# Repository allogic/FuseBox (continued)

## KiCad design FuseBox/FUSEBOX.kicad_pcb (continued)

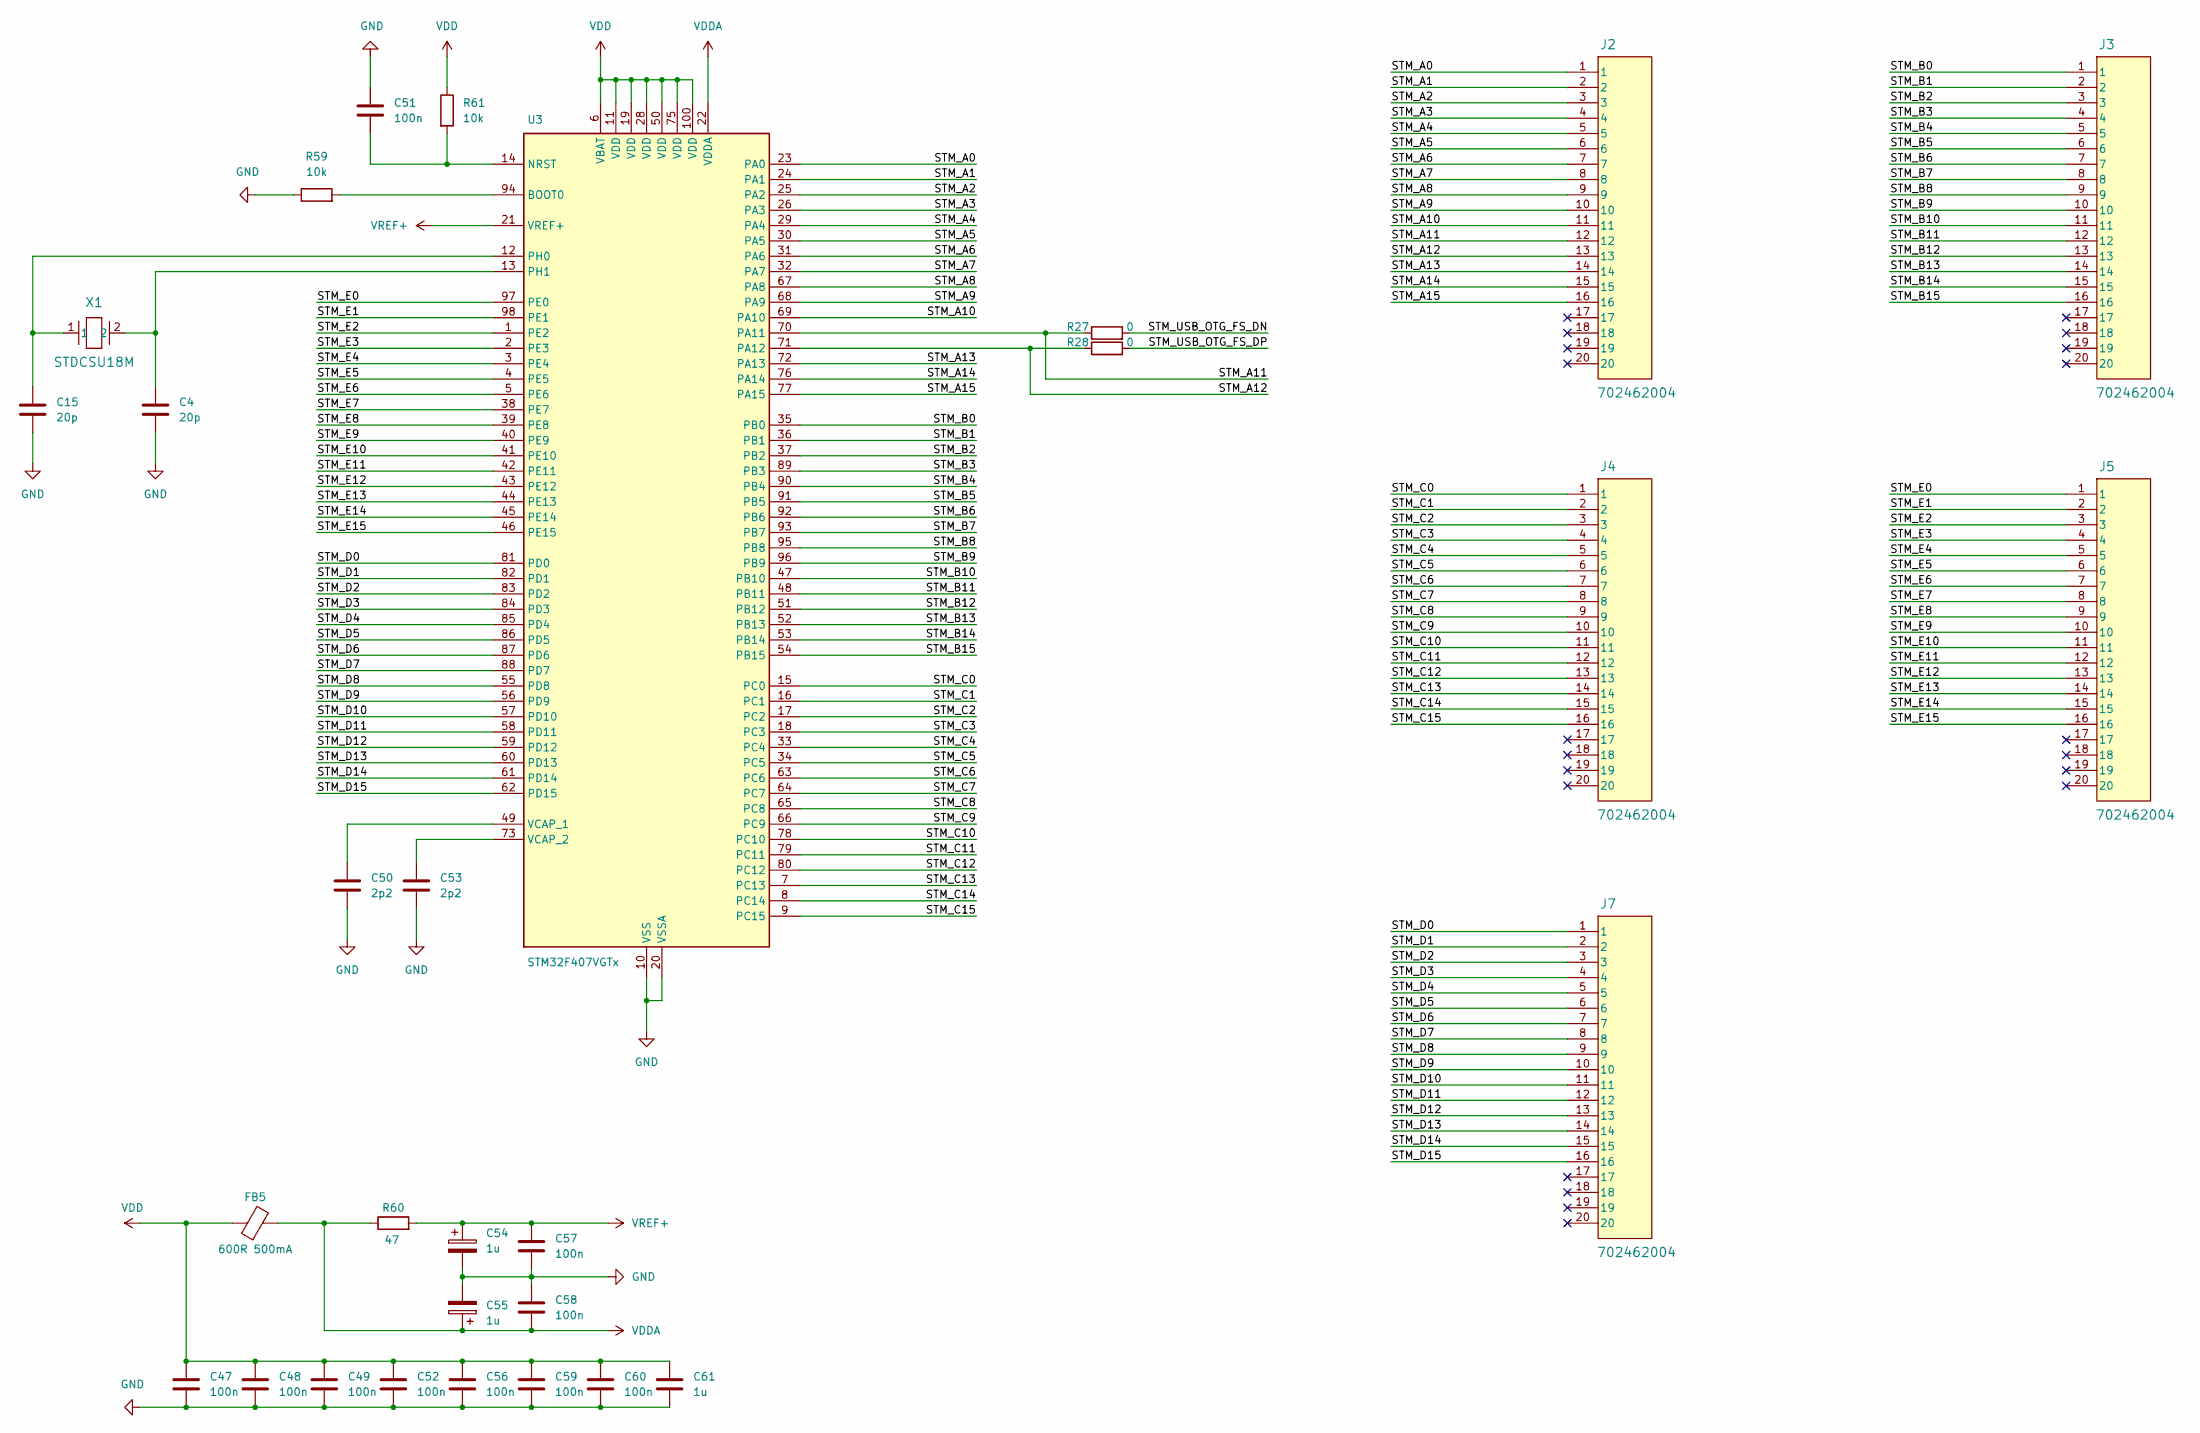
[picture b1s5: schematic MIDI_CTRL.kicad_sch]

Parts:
C4, C15: 20p; C_0603_1608Metric_Pad1.08x0.95mm_HandSolder
C47, C48, C49, C51, C52, C56, C57, C58, C59, C60: 100n; C_0603_1608Metric_Pad1.08x0.95mm_HandSolder
C50, C53: 2p2; C_0603_1608Metric_Pad1.08x0.95mm_HandSolder
C54, C55, C61: 1u; C_0603_1608Metric_Pad1.08x0.95mm_HandSolder
FB5: 600R 500mA; L_0603_1608Metric_Pad1.05x0.95mm_HandSolder
J2, J3, J4, J5, J7: 702462004
R27, R28: 0; R_0603_1608Metric_Pad0.98x0.95mm_HandSolder
R59, R61: 10k; R_0603_1608Metric_Pad0.98x0.95mm_HandSolder
R60: 47; R_0603_1608Metric_Pad0.98x0.95mm_HandSolder
U3: STM32F407VGTx; LQFP-100_14x14mm_P0.5mm
X1: STDCSU18M

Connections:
/MIDI_CTRL/STM_A0: J2.1, U3.23 (PA0)
/MIDI_CTRL/STM_A1: J2.2, U3.24 (PA1)
/MIDI_CTRL/STM_A2: J2.3, U3.25 (PA2)
/MIDI_CTRL/STM_A3: J2.4, U3.26 (PA3)
/MIDI_CTRL/STM_A4: J2.5, U3.29 (PA4)
/MIDI_CTRL/STM_A5: J2.6, U3.30 (PA5)
/MIDI_CTRL/STM_A6: J2.7, U3.31 (PA6)
/MIDI_CTRL/STM_A7: J2.8, U3.32 (PA7)
/MIDI_CTRL/STM_A8: J2.9, U3.67 (PA8)
/MIDI_CTRL/STM_A9: J2.10, U3.68 (PA9)
/MIDI_CTRL/STM_A10: J2.11, U3.69 (PA10)
/MIDI_CTRL/STM_A11: J2.12, R27.1, U3.70 (PA11)
/MIDI_CTRL/STM_A12: J2.13, R28.1, U3.71 (PA12)
/MIDI_CTRL/STM_A13: J2.14, U3.72 (PA13)
/MIDI_CTRL/STM_A14: J2.15, U3.76 (PA14)
/MIDI_CTRL/STM_A15: J2.16, U3.77 (PA15)
/MIDI_CTRL/STM_B0: J3.1, U3.35 (PB0)
/MIDI_CTRL/STM_B1: J3.2, U3.36 (PB1)
/MIDI_CTRL/STM_B2: J3.3, U3.37 (PB2)
/MIDI_CTRL/STM_B3: J3.4, U3.89 (PB3)
/MIDI_CTRL/STM_B4: J3.5, U3.90 (PB4)
/MIDI_CTRL/STM_B5: J3.6, U3.91 (PB5)
/MIDI_CTRL/STM_B6: J3.7, U3.92 (PB6)
/MIDI_CTRL/STM_B7: J3.8, U3.93 (PB7)
/MIDI_CTRL/STM_B8: J3.9, U3.95 (PB8)
/MIDI_CTRL/STM_B9: J3.10, U3.96 (PB9)
/MIDI_CTRL/STM_B10: J3.11, U3.47 (PB10)
/MIDI_CTRL/STM_B11: J3.12, U3.48 (PB11)
/MIDI_CTRL/STM_B12: J3.13, U3.51 (PB12)
/MIDI_CTRL/STM_B13: J3.14, U3.52 (PB13)
/MIDI_CTRL/STM_B14: J3.15, U3.53 (PB14)
/MIDI_CTRL/STM_B15: J3.16, U3.54 (PB15)
/MIDI_CTRL/STM_C0: J4.1, U3.15 (PC0)
/MIDI_CTRL/STM_C1: J4.2, U3.16 (PC1)
/MIDI_CTRL/STM_C2: J4.3, U3.17 (PC2)
/MIDI_CTRL/STM_C3: J4.4, U3.18 (PC3)
/MIDI_CTRL/STM_C4: J4.5, U3.33 (PC4)
/MIDI_CTRL/STM_C5: J4.6, U3.34 (PC5)
/MIDI_CTRL/STM_C6: J4.7, U3.63 (PC6)
/MIDI_CTRL/STM_C7: J4.8, U3.64 (PC7)
/MIDI_CTRL/STM_C8: J4.9, U3.65 (PC8)
/MIDI_CTRL/STM_C9: J4.10, U3.66 (PC9)
/MIDI_CTRL/STM_C10: J4.11, U3.78 (PC10)
/MIDI_CTRL/STM_C11: J4.12, U3.79 (PC11)
/MIDI_CTRL/STM_C12: J4.13, U3.80 (PC12)
/MIDI_CTRL/STM_C13: J4.14, U3.7 (PC13)
/MIDI_CTRL/STM_C14: J4.15, U3.8 (PC14)
/MIDI_CTRL/STM_C15: J4.16, U3.9 (PC15)
/MIDI_CTRL/STM_D0: J7.1, U3.81 (PD0)
/MIDI_CTRL/STM_D1: J7.2, U3.82 (PD1)
/MIDI_CTRL/STM_D2: J7.3, U3.83 (PD2)
/MIDI_CTRL/STM_D3: J7.4, U3.84 (PD3)
/MIDI_CTRL/STM_D4: J7.5, U3.85 (PD4)
/MIDI_CTRL/STM_D5: J7.6, U3.86 (PD5)
/MIDI_CTRL/STM_D6: J7.7, U3.87 (PD6)
/MIDI_CTRL/STM_D7: J7.8, U3.88 (PD7)
/MIDI_CTRL/STM_D8: J7.9, U3.55 (PD8)
/MIDI_CTRL/STM_D9: J7.10, U3.56 (PD9)
/MIDI_CTRL/STM_D10: J7.11, U3.57 (PD10)
/MIDI_CTRL/STM_D11: J7.12, U3.58 (PD11)
/MIDI_CTRL/STM_D12: J7.13, U3.59 (PD12)
/MIDI_CTRL/STM_D13: J7.14, U3.60 (PD13)
/MIDI_CTRL/STM_D14: J7.15, U3.61 (PD14)
/MIDI_CTRL/STM_D15: J7.16, U3.62 (PD15)
/MIDI_CTRL/STM_E0: J5.1, U3.97 (PE0)
/MIDI_CTRL/STM_E1: J5.2, U3.98 (PE1)
/MIDI_CTRL/STM_E2: J5.3, U3.1 (PE2)
/MIDI_CTRL/STM_E3: J5.4, U3.2 (PE3)
/MIDI_CTRL/STM_E4: J5.5, U3.3 (PE4)
/MIDI_CTRL/STM_E5: J5.6, U3.4 (PE5)
/MIDI_CTRL/STM_E6: J5.7, U3.5 (PE6)
/MIDI_CTRL/STM_E7: J5.8, U3.38 (PE7)
/MIDI_CTRL/STM_E8: J5.9, U3.39 (PE8)
/MIDI_CTRL/STM_E9: J5.10, U3.40 (PE9)
/MIDI_CTRL/STM_E10: J5.11, U3.41 (PE10)
/MIDI_CTRL/STM_E11: J5.12, U3.42 (PE11)
/MIDI_CTRL/STM_E12: J5.13, U3.43 (PE12)
/MIDI_CTRL/STM_E13: J5.14, U3.44 (PE13)
/MIDI_CTRL/STM_E14: J5.15, U3.45 (PE14)
/MIDI_CTRL/STM_E15: J5.16, U3.46 (PE15)
/MIDI_CTRL/STM_USB_OTG_FS_DN: R27.2
/MIDI_CTRL/STM_USB_OTG_FS_DP: R28.2
GND: C4.1, C15.1, C47.2, C48.2, C49.2, C50.2, C51.2, C52.2, C53.2, C54.2, C55.2, C56.2, C57.2, C58.1, C59.2, C60.2, C61.2, R59.1, U3.10 (VSS), U3.20 (VSSA), U3.27 (VSS), U3.74 (VSS), U3.99 (VSS); also elsewhere on the board
unnamed: R59.2, U3.94 (BOOT0)
unnamed: C51.1, R61.2, U3.14 (NRST)
unnamed: C15.2, U3.12 (PH0), X1.1
unnamed: C4.2, U3.13 (PH1), X1.2
unnamed: C50.1, U3.49 (VCAP_1)
unnamed: C53.1, U3.73 (VCAP_2)
VDD: C47.1, C48.1, C49.1, C52.1, C56.1, C59.1, C60.1, C61.1, FB5.1, R61.1, U3.6 (VBAT), U3.11 (VDD), U3.19 (VDD), U3.28 (VDD), U3.50 (VDD), U3.75 (VDD), U3.100 (VDD)
VDDA: C55.1, C58.2, FB5.2, R60.1, U3.22 (VDDA)
VREF+: C54.1, C57.1, R60.2, U3.21 (VREF+)

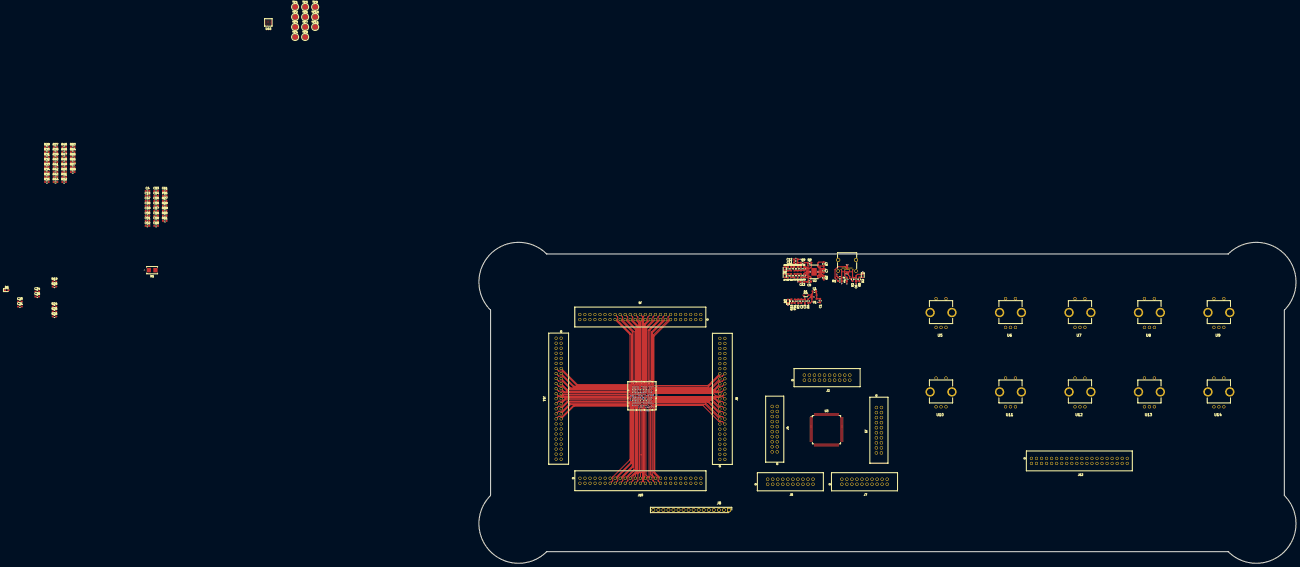
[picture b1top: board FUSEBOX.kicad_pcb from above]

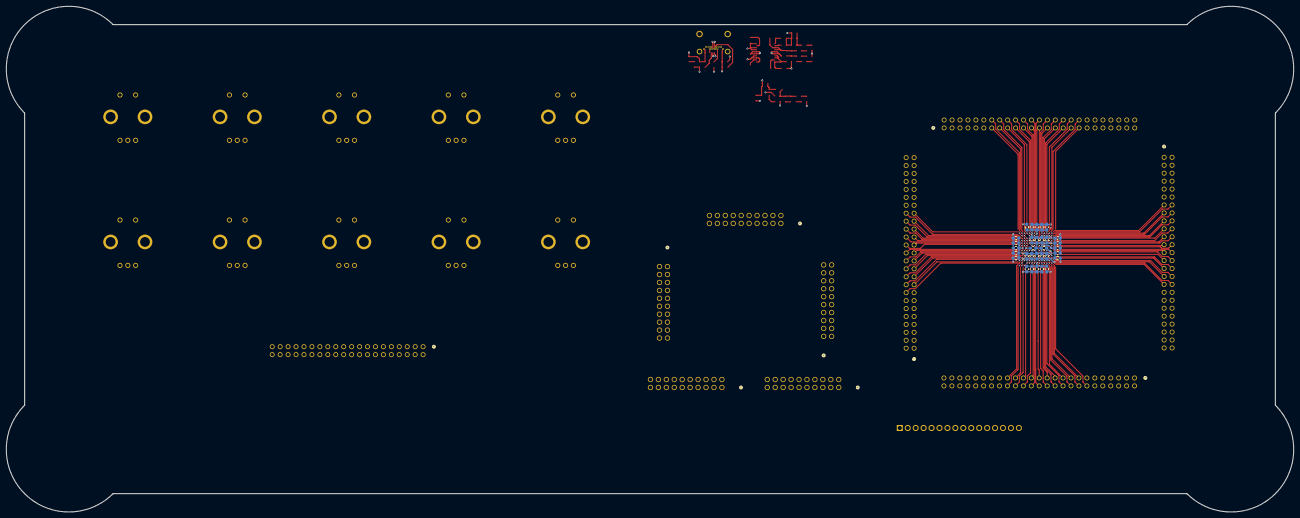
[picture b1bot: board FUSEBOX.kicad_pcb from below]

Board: 6 copper layers, 411.7 x 161.7 mm, 173 parts (31 on the bottom side), 355 nets.

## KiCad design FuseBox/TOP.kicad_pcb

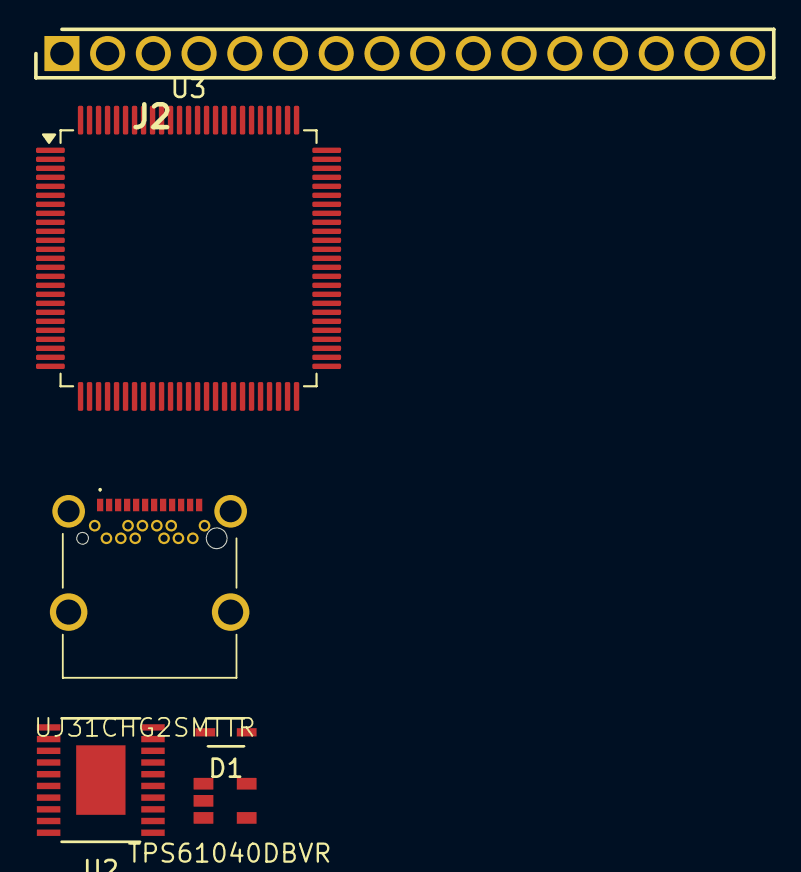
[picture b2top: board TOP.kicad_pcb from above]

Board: 2 copper layers, 6 parts (0 on the bottom side), 9 nets, no tracks yet.

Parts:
D1: CUS10S40H3F
J1: UJ31CHG2SMTTR
J2: 61301611121
U1: TPS61040DBVR
U2: LT3030EFETRPBF; LT8302ES8ETRPBF
U3: STM32F407VGTx; LQFP-100_14x14mm_P0.5mm

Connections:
+1V22: U2.7 (OUT2), U2.8 (OUT2), U2.10 (ADJ2)
+3V31: U2.3 (OUT1), U2.4 (OUT1)
+5V: U1.4 (EN), U1.5 (VIN), U2.11 (*SHDN2), U2.13 (IN2), U2.14 (IN2), U2.17 (IN1), U2.18 (IN1), U2.20 (*SHDN1)
/USB_OTG_FS_DN: J1.A7 (DN1), J1.B7 (DN2)
/USB_OTG_FS_DP: J1.A6 (DP1), J1.B6 (DP2)
GND: J1.A1 (GND_1), J1.A12 (GND_2), J1.B1 (GND_3), J1.B12 (GND_4), J1.S1 (GND_5), J1.S2 (GND_6), J1.S3 (GND_7), J1.S4 (GND_8), U1.2 (GND), U2.5 (GND), U2.6 (GND), U2.15 (GND), U2.16 (GND)
unnamed: D1.2, U1.1 (SW)
unnamed: U3.10 (VSS), U3.27 (VSS), U3.74 (VSS), U3.99 (VSS)
VBUS: J1.A4 (V_BUS_1), J1.A9 (V_BUS_2), J1.B4 (VBUS_1), J1.B9 (VBUS_2)

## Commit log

2025-12-08 First PWR iteration
2025-12-09 added models
2025-12-09 Added STM32F4
2025-12-09 some foo
2025-12-10 added ICE40HX
2025-12-10 added temp USB controllers
2025-12-10 added molex terminals
2025-12-11 finished schematic
2025-12-12 layout
2025-12-12 some bar
2025-12-15 fpga decoupling
2025-12-15 bank 2 done
2025-12-16 bank L done
2025-12-17 more traces
2025-12-18 added again some traces
2025-12-18 preps for crosslink and DDR3
2025-12-19 added a reference
2026-01-06 kekw
2026-01-06 keeeek
2026-01-08 more kekw
2026-01-08 changuz
2026-01-13 stupid analog
